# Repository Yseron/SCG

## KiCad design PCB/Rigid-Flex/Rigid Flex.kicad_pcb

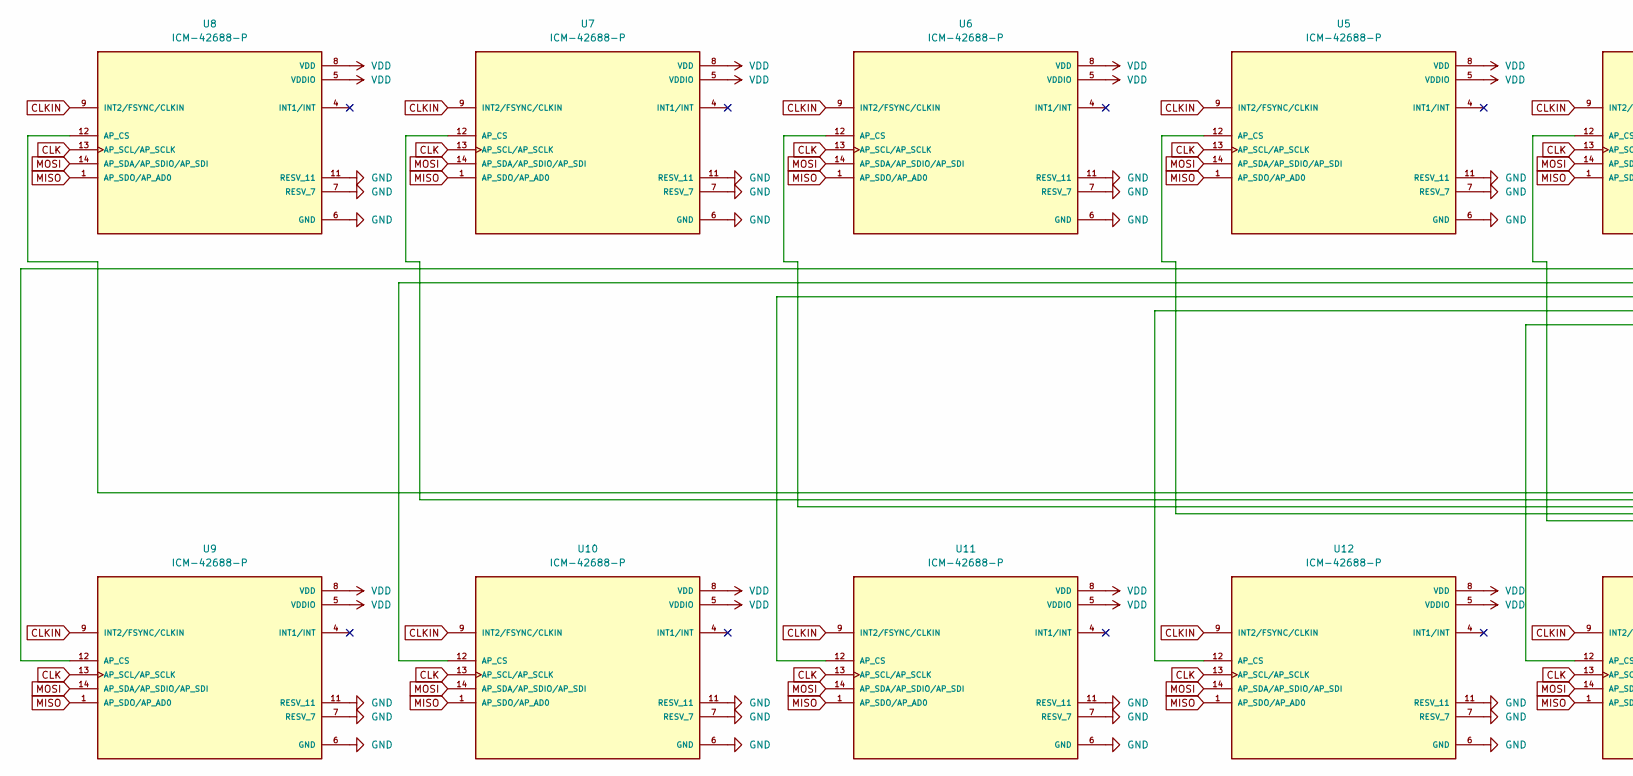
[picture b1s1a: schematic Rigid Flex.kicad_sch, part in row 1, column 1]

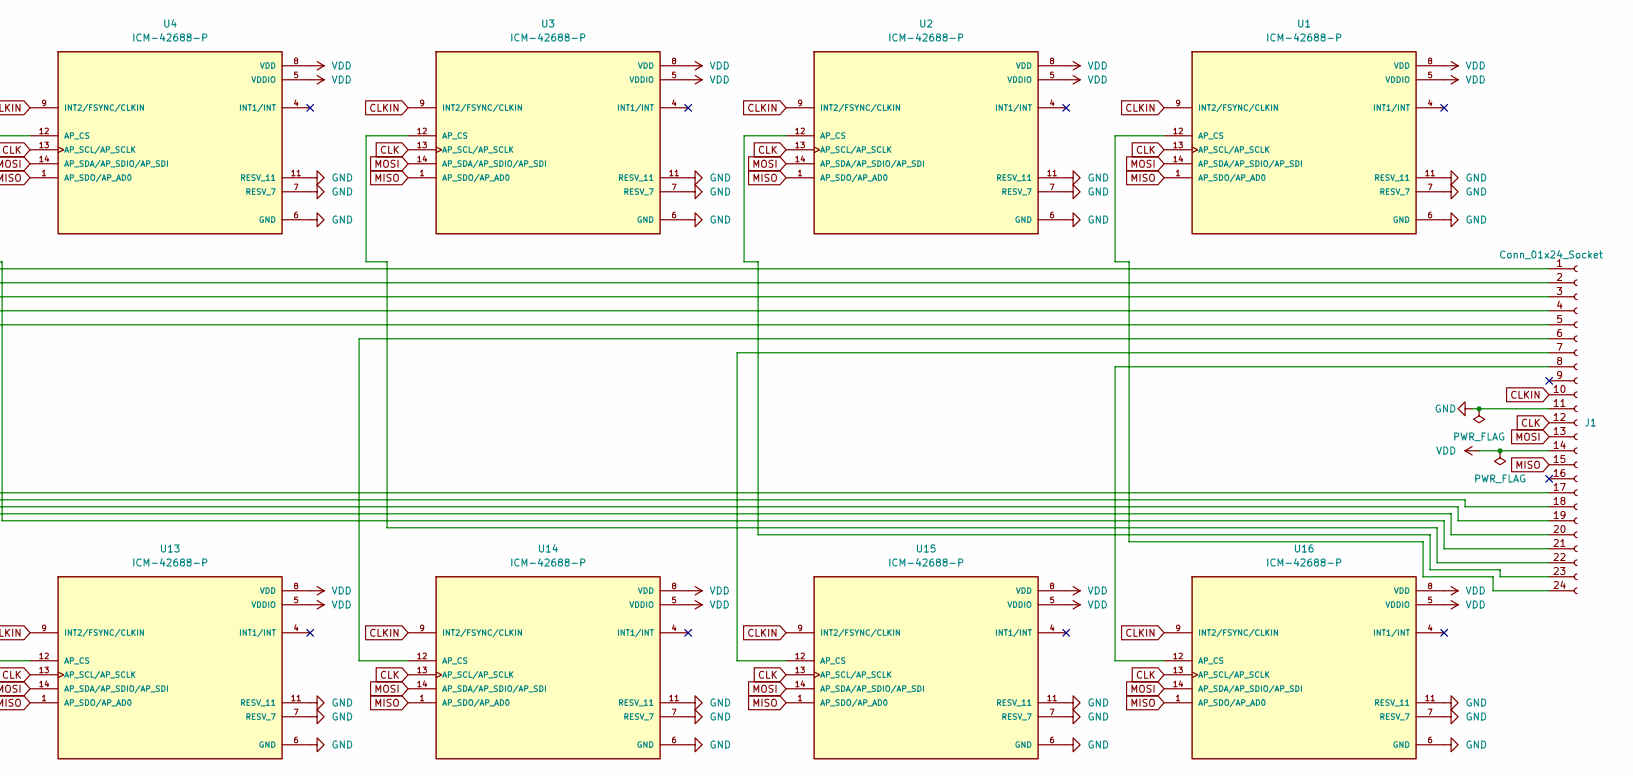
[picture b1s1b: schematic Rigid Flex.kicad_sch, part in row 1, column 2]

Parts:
J1: Conn_01x24_Socket; Molex_502244-2430_1x24-1MP_P0.5mm_Horizontal
U1, U2, U3, U4, U5, U6, U7, U8, U9, U10, U11, U12, U13, U14, U15, U16: ICM-42688-P; PQFN50P300X250X97-14N; PARTREV 1.2

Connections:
CLK: J1.12, U1.13 (AP_SCL/AP_SCLK), U2.13 (AP_SCL/AP_SCLK), U3.13 (AP_SCL/AP_SCLK), U4.13 (AP_SCL/AP_SCLK), U5.13 (AP_SCL/AP_SCLK), U6.13 (AP_SCL/AP_SCLK), U7.13 (AP_SCL/AP_SCLK), U8.13 (AP_SCL/AP_SCLK), U9.13 (AP_SCL/AP_SCLK), U10.13 (AP_SCL/AP_SCLK), U11.13 (AP_SCL/AP_SCLK), U12.13 (AP_SCL/AP_SCLK), U13.13 (AP_SCL/AP_SCLK), U14.13 (AP_SCL/AP_SCLK), U15.13 (AP_SCL/AP_SCLK), U16.13 (AP_SCL/AP_SCLK)
CLKIN: J1.10, U1.9 (INT2/FSYNC/CLKIN), U2.9 (INT2/FSYNC/CLKIN), U3.9 (INT2/FSYNC/CLKIN), U4.9 (INT2/FSYNC/CLKIN), U5.9 (INT2/FSYNC/CLKIN), U6.9 (INT2/FSYNC/CLKIN), U7.9 (INT2/FSYNC/CLKIN), U8.9 (INT2/FSYNC/CLKIN), U9.9 (INT2/FSYNC/CLKIN), U10.9 (INT2/FSYNC/CLKIN), U11.9 (INT2/FSYNC/CLKIN), U12.9 (INT2/FSYNC/CLKIN), U13.9 (INT2/FSYNC/CLKIN), U14.9 (INT2/FSYNC/CLKIN), U15.9 (INT2/FSYNC/CLKIN), U16.9 (INT2/FSYNC/CLKIN)
GND: J1.11, U1.6 (GND), U1.7 (RESV_7), U1.11 (RESV_11), U2.6 (GND), U2.7 (RESV_7), U2.11 (RESV_11), U3.6 (GND), U3.7 (RESV_7), U3.11 (RESV_11), U4.6 (GND), U4.7 (RESV_7), U4.11 (RESV_11), U5.6 (GND), U5.7 (RESV_7), U5.11 (RESV_11), U6.6 (GND), U6.7 (RESV_7), U6.11 (RESV_11), U7.6 (GND), U7.7 (RESV_7), U7.11 (RESV_11), U8.6 (GND), U8.7 (RESV_7), U8.11 (RESV_11), U9.6 (GND), U9.7 (RESV_7), U9.11 (RESV_11), U10.6 (GND), U10.7 (RESV_7), U10.11 (RESV_11), U11.6 (GND), U11.7 (RESV_7), U11.11 (RESV_11), U12.6 (GND), U12.7 (RESV_7), U12.11 (RESV_11), U13.6 (GND), U13.7 (RESV_7), U13.11 (RESV_11), U14.6 (GND), U14.7 (RESV_7), U14.11 (RESV_11), U15.6 (GND), U15.7 (RESV_7), U15.11 (RESV_11), U16.6 (GND), U16.7 (RESV_7), U16.11 (RESV_11)
MISO: J1.15, U1.1 (AP_SDO/AP_AD0), U2.1 (AP_SDO/AP_AD0), U3.1 (AP_SDO/AP_AD0), U4.1 (AP_SDO/AP_AD0), U5.1 (AP_SDO/AP_AD0), U6.1 (AP_SDO/AP_AD0), U7.1 (AP_SDO/AP_AD0), U8.1 (AP_SDO/AP_AD0), U9.1 (AP_SDO/AP_AD0), U10.1 (AP_SDO/AP_AD0), U11.1 (AP_SDO/AP_AD0), U12.1 (AP_SDO/AP_AD0), U13.1 (AP_SDO/AP_AD0), U14.1 (AP_SDO/AP_AD0), U15.1 (AP_SDO/AP_AD0), U16.1 (AP_SDO/AP_AD0)
MOSI: J1.13, U1.14 (AP_SDA/AP_SDIO/AP_SDI), U2.14 (AP_SDA/AP_SDIO/AP_SDI), U3.14 (AP_SDA/AP_SDIO/AP_SDI), U4.14 (AP_SDA/AP_SDIO/AP_SDI), U5.14 (AP_SDA/AP_SDIO/AP_SDI), U6.14 (AP_SDA/AP_SDIO/AP_SDI), U7.14 (AP_SDA/AP_SDIO/AP_SDI), U8.14 (AP_SDA/AP_SDIO/AP_SDI), U9.14 (AP_SDA/AP_SDIO/AP_SDI), U10.14 (AP_SDA/AP_SDIO/AP_SDI), U11.14 (AP_SDA/AP_SDIO/AP_SDI), U12.14 (AP_SDA/AP_SDIO/AP_SDI), U13.14 (AP_SDA/AP_SDIO/AP_SDI), U14.14 (AP_SDA/AP_SDIO/AP_SDI), U15.14 (AP_SDA/AP_SDIO/AP_SDI), U16.14 (AP_SDA/AP_SDIO/AP_SDI)
unnamed: J1.1, U9.12 (AP_CS)
unnamed: J1.2, U10.12 (AP_CS)
unnamed: J1.3, U11.12 (AP_CS)
unnamed: J1.4, U12.12 (AP_CS)
unnamed: J1.5, U13.12 (AP_CS)
unnamed: J1.6, U14.12 (AP_CS)
unnamed: J1.7, U15.12 (AP_CS)
unnamed: J1.8, U16.12 (AP_CS)
unnamed: J1.17, U8.12 (AP_CS)
unnamed: J1.18, U7.12 (AP_CS)
unnamed: J1.19, U6.12 (AP_CS)
unnamed: J1.20, U5.12 (AP_CS)
unnamed: J1.21, U4.12 (AP_CS)
unnamed: J1.22, U3.12 (AP_CS)
unnamed: J1.23, U2.12 (AP_CS)
unnamed: J1.24, U1.12 (AP_CS)
VDD: J1.14, U1.5 (VDDIO), U1.8 (VDD), U2.5 (VDDIO), U2.8 (VDD), U3.5 (VDDIO), U3.8 (VDD), U4.5 (VDDIO), U4.8 (VDD), U5.5 (VDDIO), U5.8 (VDD), U6.5 (VDDIO), U6.8 (VDD), U7.5 (VDDIO), U7.8 (VDD), U8.5 (VDDIO), U8.8 (VDD), U9.5 (VDDIO), U9.8 (VDD), U10.5 (VDDIO), U10.8 (VDD), U11.5 (VDDIO), U11.8 (VDD), U12.5 (VDDIO), U12.8 (VDD), U13.5 (VDDIO), U13.8 (VDD), U14.5 (VDDIO), U14.8 (VDD), U15.5 (VDDIO), U15.8 (VDD), U16.5 (VDDIO), U16.8 (VDD)

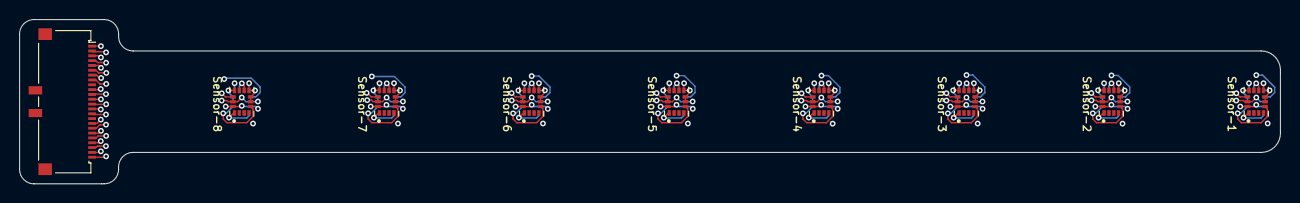
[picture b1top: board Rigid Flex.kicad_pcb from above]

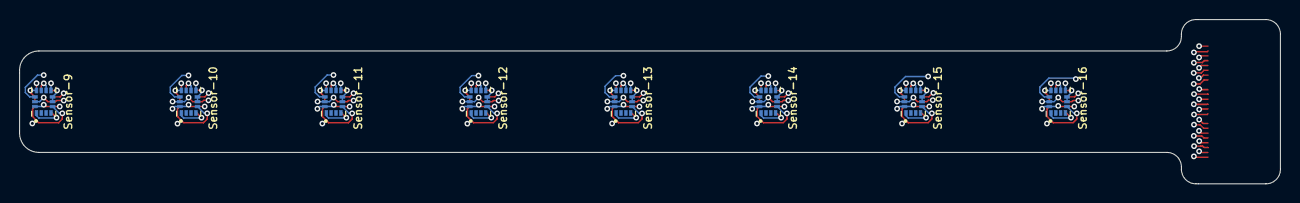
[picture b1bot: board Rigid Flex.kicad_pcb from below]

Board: 4 copper layers, 130.5 x 17.0 mm, 17 parts (8 on the bottom side), 22 nets.

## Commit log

2025-07-29 Inital commit
2025-07-31 Testing
2025-08-04 ENTDAA loop
2025-08-04 Added defines
2025-08-08 Update & added example
2025-08-12 Finished I3C testing
2025-08-12 Created
2025-08-13 Single transmit
2025-08-14 SPI works
2025-08-15 Started implementing
2025-08-15 Added defines, started commenting
2025-08-16 Finished comments
2025-08-18 Nix funktioniert?
2025-08-19 Working on reading FIFO
2025-08-19 Fertig für heute
2025-08-20 ka digga
2025-08-21 Sensor programming done in theory
2025-09-15 Added from previous project
2025-09-16 Create test
2025-09-16 Create files
2025-09-26 Did stuff
2025-09-26 Es funktioniert
2025-09-29 Läuft
2025-09-29 Added comments
2025-10-02 FIFO works
2025-11-10 Added FlushFIFO
2025-11-12 Sachen
2025-11-14 Done
